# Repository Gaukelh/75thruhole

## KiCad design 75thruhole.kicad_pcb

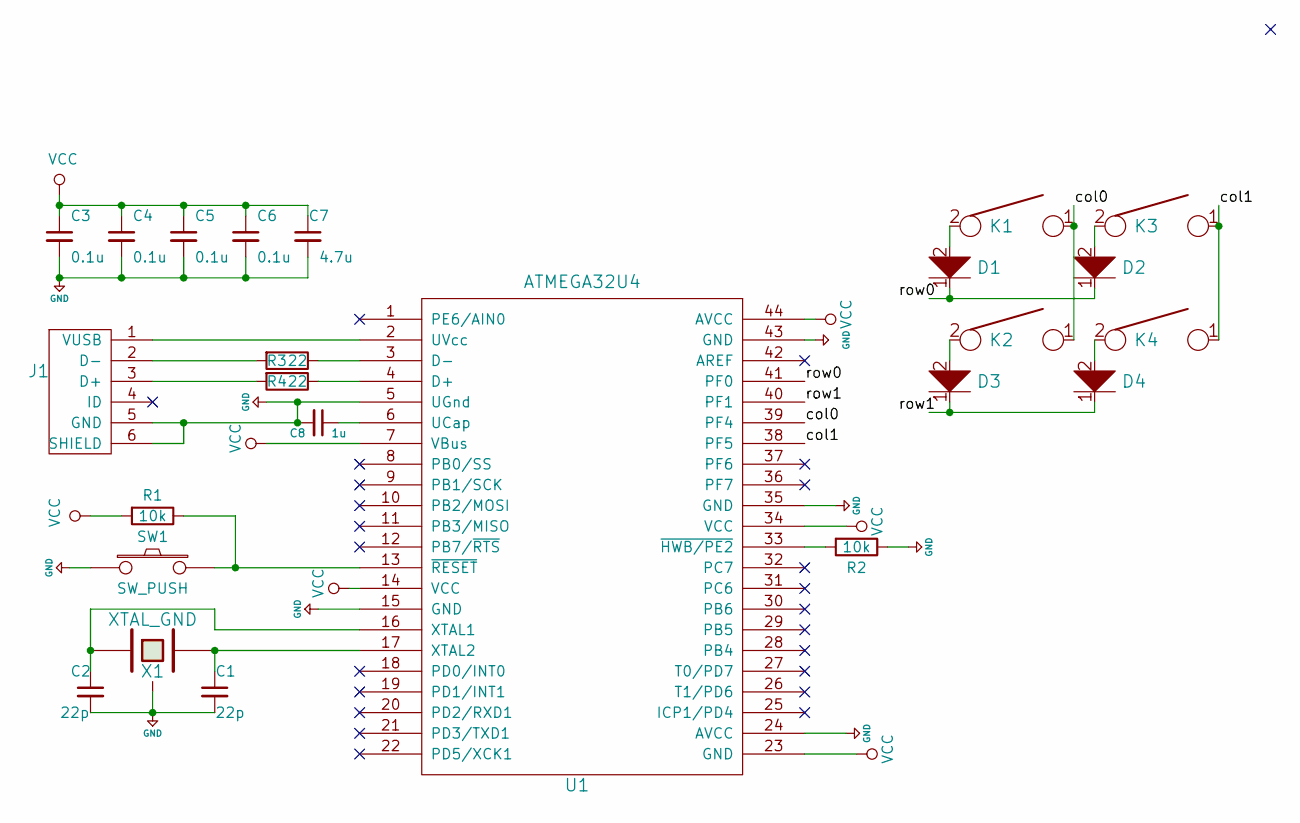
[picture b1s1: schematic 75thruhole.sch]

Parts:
C1, C2: 22p
C3, C4, C5, C6: 0.1u
C7: 4.7u
C8: 1u
D1, D2, D3, D4: D
J1: USB_mini_micro_B
K1, K2, K3, K4: KEYSW
R1, R2: 10k
R3, R4: 22
SW1: SW_PUSH
U1: ATMEGA32U4
X1: XTAL_GND

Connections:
+5V: C1.2, C2.2, C3.2, C4.2, C5.2, C6.2, C7.2, C8.2, J1.5 (GND), J1.6 (SHIELD), R2.1, SW1.1, U1.5 (UGnd), U1.15 (GND), U1.24 (AVCC), U1.35 (GND), U1.43 (GND), X1.3
/col0: K1.1, K2.1, U1.39 (PF4)
/col1: K3.1, K4.1, U1.38 (PF5)
/row0: U1.41 (PF0)
/row1: U1.40 (PF1)
unnamed: C1.1, U1.17 (XTAL2), X1.2
unnamed: C2.1, U1.16 (XTAL1), X1.1
unnamed: C8.1, U1.6 (UCap)
unnamed: D1.1, D2.1
unnamed: D1.2, K1.2
unnamed: D2.2, K3.2
unnamed: D3.1, D4.1
unnamed: D3.2, K2.2
unnamed: D4.2, K4.2
unnamed: J1.1 (VUSB), U1.2 (UVcc)
unnamed: J1.2 (D-), R3.2
unnamed: J1.3 (D+), R4.2
unnamed: R1.1, SW1.2, U1.13 (~RESET)
unnamed: R2.2, U1.33 (~HWB/PE2)
unnamed: R3.1, U1.3 (D-)
unnamed: R4.1, U1.4 (D+)
VCC: C3.1, C4.1, C5.1, C6.1, C7.1, R1.2, U1.7 (VBus), U1.14 (VCC), U1.23 (GND), U1.34 (VCC), U1.44 (AVCC)

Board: 2 copper layers, 24 parts (0 on the bottom side), 20 nets, no tracks yet.

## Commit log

2020-02-10 first
2020-02-10 put in keys
2020-02-10 matching
2020-02-11 generate pcb
